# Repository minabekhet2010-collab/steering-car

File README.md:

https://www.tinkercad.com/things/55mr5SuFU7E-steering-car/editel?sharecode=2z4cLL54SJwKaxQAOSbbML9kBKHUp745pwz4nTn32Xg

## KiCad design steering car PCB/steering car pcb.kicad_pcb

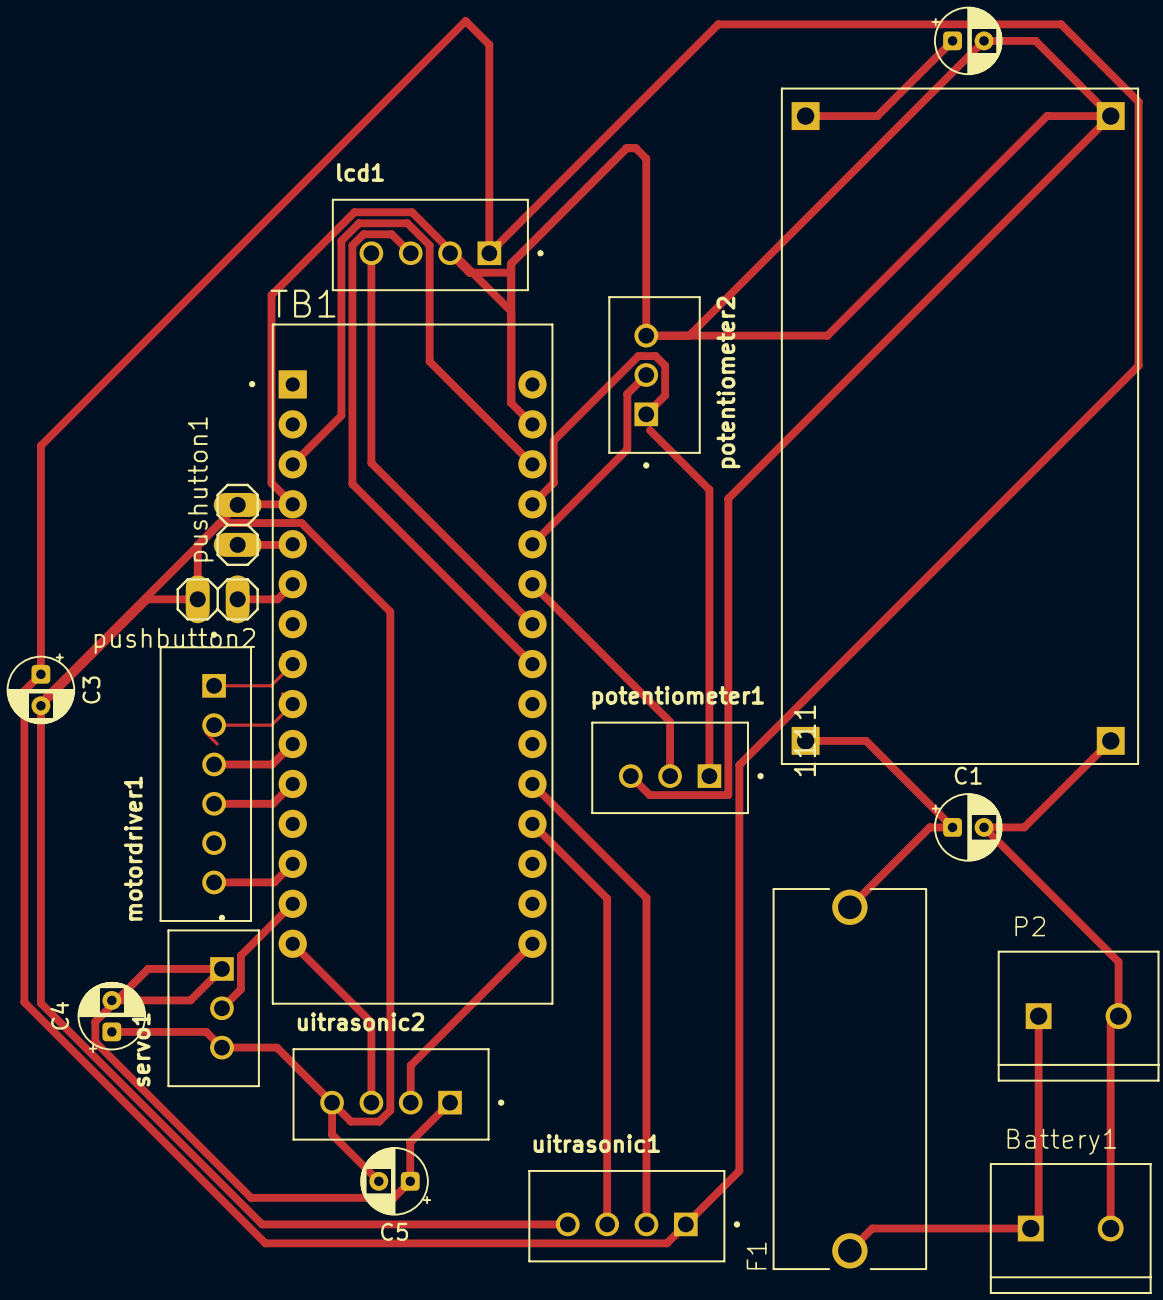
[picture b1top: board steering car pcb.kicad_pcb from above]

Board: 2 copper layers, 19 parts (0 on the bottom side), 23 nets.

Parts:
1111: LM2596
Battery1: TE_282837-2
C1, C2, C3: 470uF; CP_Radial_D4.0mm_P2.00mm
C4, C5: 100uF; CP_Radial_D4.0mm_P2.00mm
F1: FUSE_4527
P2: TE_282837-2
TB1: SHIELD_ARDUINO_NANO
lcd1: JST_B4B-XH-A(LF)(SN)
motordriver1: JST_B6B-XH-A(LF)(SN)
potentiometer1, potentiometer2: JST_B3B-XH-A_(LF)(SN)
pushbutton2: 1X02
pushutton1: 1X02
servo1: JST_B3B-XH-A_(LF)(SN)
uitrasonic1, uitrasonic2: JST_B4B-XH-A(LF)(SN)

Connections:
/In2: TB1.10 (D7), motordriver1.3
/In3: TB1.11 (D8), motordriver1.4
/a1: TB1.25 (A6), potentiometer1.2
/a2: TB1.26 (A7), potentiometer2.2
/a4: TB1.23 (A4), lcd1.3
/a5: TB1.24 (A5), lcd1.4
/d2: TB1.5 (D2), pushutton1.1
/d3: TB1.6 (D3), pushbutton2.1
/d11: TB1.14 (D11/MOSI), servo1.2
/echo1: TB1.19 (A0), uitrasonic1.3
/echo2: TB1.15 (D12/MISO), uitrasonic2.3
/ena: TB1.13 (D10), motordriver1.6
/enb: TB1.8 (D5), motordriver1.1
/fuse: Battery1.1, F1.1, P2.1
/in1: TB1.9 (D6), motordriver1.2
/trig1: TB1.20 (A1), uitrasonic1.2
/trig2: TB1.16 (D13/SCK), uitrasonic2.2
GND: 1111.OUT-, C2.2, C3.2, C4.1, C5.2, TB1.4 (COM/GND), TB1.29 (COM/GND), lcd1.2, potentiometer1.3, potentiometer2.3, pushbutton2.2, pushutton1.2, servo1.3, uitrasonic1.4, uitrasonic2.4
GND1: 1111.IN-, Battery1.2, C1.2, P2.2
unnamed: 1111.IN+, C1.1, F1.2
unnamed: 1111.OUT+, C2.1
unnamed: TB1.3 (RESET), TB1.28 (RESET)
VCC: C3.1, C4.2, C5.1, TB1.27 (+5V), lcd1.1, potentiometer1.1, potentiometer2.1, servo1.1, uitrasonic1.1, uitrasonic2.1
